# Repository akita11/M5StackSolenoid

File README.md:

# M5StackSolenoid

ソレノイド（[タカハの5Vソレノイド](http://takaha.co.jp/co/product-ss#productWrapSec1)など）を制御するM5Stack用の拡張基板です。
最大4個のソレノイドをON/OFF制御できます。

# 機能

実装するコネクタ・部品によって、以下の2通りの使い方ができます。
- [使い方1] USBコネクタ実装（[タカハの5Vソレノイド](http://takaha.co.jp/co/product-ss#productWrapSec1)用）：以下のようになります

- [使い方2] 2.ネジ端子実装（一般のソレノイド）：以下のようになります

※[スイッチサイエンスで託販売しているもの](https://www.switch-science.com/catalog/6328/)（5Vソレノイド用のショートピン端子が5個付属しています）は、「使い方1」の状態のものです。

# 用意するもの
- M5Stack (Core/Gray等のCore系、またはCore2)
- USB Type-C端子のある電源（ACアダプタ、モバイルバッテリ等。ソレノイド駆動用の電源）
- ソレノイド（用いているnMOS、ダイオードの定格内のものを用いてください）
  - [使い方1] [タカハの5Vソレノイド](http://takaha.co.jp/co/product-ss#productWrapSec1)、microUSBケーブル、[ショートピン端子](http://akizukidenshi.com/catalog/g/gP-03687/)※「タカハの5Vソレノイド」に「ショートピン端子」を差し込んだ状態で使用します
  - [使い方2] ソレノイド、ネジ端子[HT396R-4P](https://ja.aliexpress.com/item/33027266661.html)、IP2721（USB PDで5V以外の電圧をソレノイド駆動に用いる場合：IP2721の使い方の詳細はIP2721のデータシートを参照してください）

# 使い方
1. M5Stackの本体(Core、底板を外した状態)に本ボードを差し込み、USB Type-C端子に電源をつなぎます。
1. M5Stackの以下のGPIOピンに1を与えるとソレノイドがONに、0を与えるとOFFになります。（M5Stackのプログラムは、ArduinoIDE、UI Flow等で開発できます）使用例としてtest.m5f (UI Flowプログラム）を参照してください。
   - Ch.A : GPIO26
   - Ch.B : GPIO12 (Core2ではGPIO27)
   - Ch.C : GPIO13 (Core2ではGPIO19)
   - Ch.D : GPIO5 (Core2ではGPIO33)

※なおソレノイドの番号は、[使い方1]の場合は基板上の[A]-[D]で表示されているUSBコネクタに対応します。[使い方2]の場合は、基板上の"Ch.A"-"Ch.D"の表示に対応し、1つのネジ端子(HT396R)に2個のソレノイドを接続できます。

# Author

Junichi Akita (@akita11, akita@ifdl.jp)

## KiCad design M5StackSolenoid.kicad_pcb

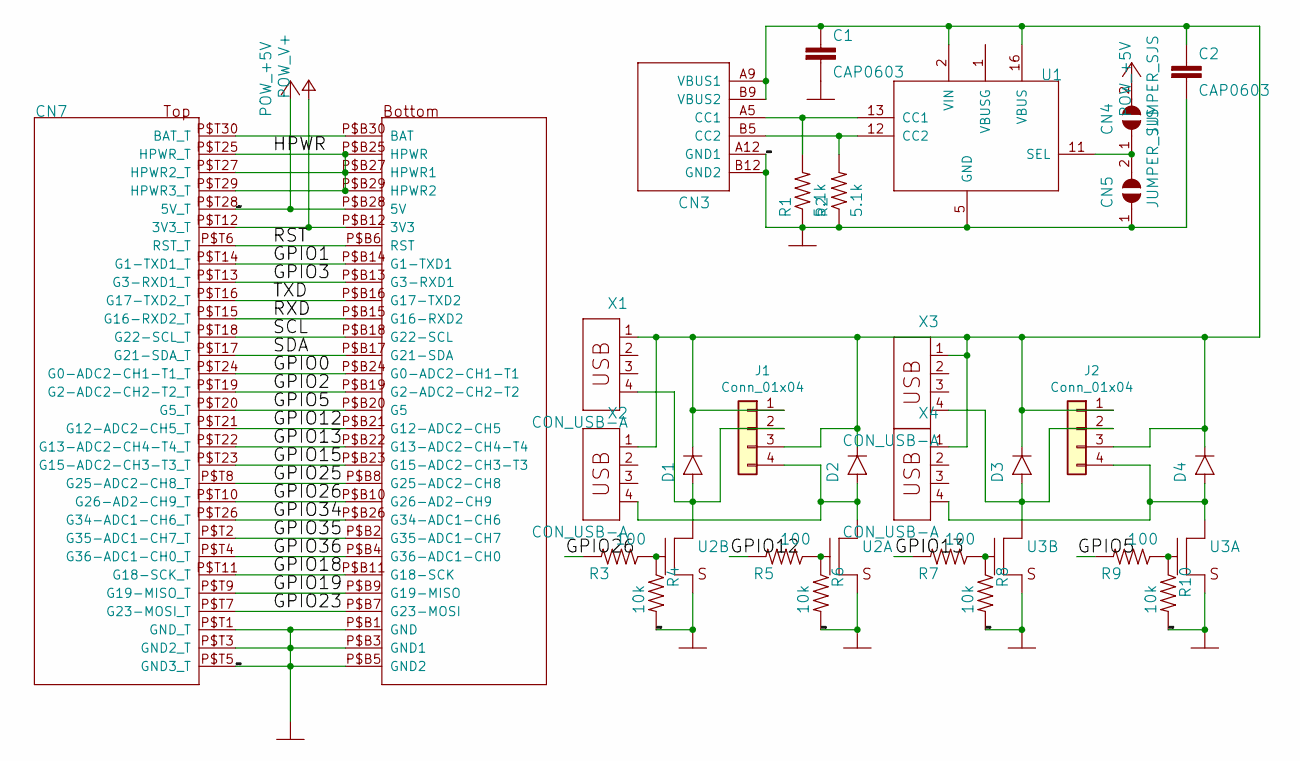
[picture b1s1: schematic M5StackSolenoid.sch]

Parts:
C1, C2: CAP0603; 0603
CN3: CON_USB-C-6; USB-C_6P
CN4, CN5: JUMPER_SJS
CN7: MBUS_SEPNOHOLE; MBUS_SEP_NOHOLENOTCH
D1, D2, D3, D4: DIODESOD123FL; SOD123FL
J1, J2: Conn_01x04; CON_HT396R_4P
R1, R2: 5.1k; 0603
R3, R5, R7, R9: 100; 0603
R4, R6, R8, R10: 10k; 0603
U1: PMC_IP2721; TSSOP16
U2, U3: TR_NMOS_IRF7103; SO08
X1, X2, X3, X4: CON_USB-A; USB-A

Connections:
+5V: CN4.2, CN7.P$B28 (5V), CN7.P$T28 (5V_T)
/GPIO0: CN7.P$B24 (G0-ADC2-CH1-T1), CN7.P$T24 (G0-ADC2-CH1-T1_T)
/GPIO1: CN7.P$B14 (G1-TXD1), CN7.P$T14 (G1-TXD1_T)
/GPIO2: CN7.P$B19 (G2-ADC2-CH2-T2), CN7.P$T19 (G2-ADC2-CH2-T2_T)
/GPIO3: CN7.P$B13 (G3-RXD1), CN7.P$T13 (G3-RXD1_T)
/GPIO5: CN7.P$B20 (G5), CN7.P$T20 (G5_T), R9.2
/GPIO12: CN7.P$B21 (G12-ADC2-CH5), CN7.P$T21 (G12-ADC2-CH5_T), R5.2
/GPIO13: CN7.P$B22 (G13-ADC2-CH4-T4), CN7.P$T22 (G13-ADC2-CH4-T4_T), R7.2
/GPIO15: CN7.P$B23 (G15-ADC2-CH3-T3), CN7.P$T23 (G15-ADC2-CH3-T3_T)
/GPIO18: CN7.P$B11 (G18-SCK), CN7.P$T11 (G18-SCK_T)
/GPIO19: CN7.P$B9 (G19-MISO), CN7.P$T9 (G19-MISO_T)
/GPIO23: CN7.P$B7 (G23-MOSI), CN7.P$T7 (G23-MOSI_T)
/GPIO25: CN7.P$B8 (G25-ADC2-CH8), CN7.P$T8 (G25-ADC2-CH8_T)
/GPIO26: CN7.P$B10 (G26-AD2-CH9), CN7.P$T10 (G26-AD2-CH9_T), R3.2
/GPIO34: CN7.P$B26 (G34-ADC1-CH6), CN7.P$T26 (G34-ADC1-CH6_T)
/GPIO35: CN7.P$B2 (G35-ADC1-CH7), CN7.P$T2 (G35-ADC1-CH7_T)
/GPIO36: CN7.P$B4 (G36-ADC1-CH0), CN7.P$T4 (G36-ADC1-CH0_T)
/HPWR: CN7.P$B25 (HPWR), CN7.P$B27 (HPWR1), CN7.P$B29 (HPWR2), CN7.P$T25 (HPWR_T), CN7.P$T27 (HPWR2_T), CN7.P$T29 (HPWR3_T)
/RST: CN7.P$B6 (RST), CN7.P$T6 (RST_T)
/RXD: CN7.P$B15 (G16-RXD2), CN7.P$T15 (G16-RXD2_T)
/SCL: CN7.P$B18 (G22-SCL), CN7.P$T18 (G22-SCL_T)
/SDA: CN7.P$B17 (G21-SDA), CN7.P$T17 (G21-SDA_T)
/TXD: CN7.P$B16 (G17-TXD2), CN7.P$T16 (G17-TXD2_T)
GND: C1.2, C2.2, CN3.A12 (GND1), CN3.B12 (GND2), CN5.1, CN7.P$B1 (GND), CN7.P$B3 (GND1), CN7.P$B5 (GND2), CN7.P$T1 (GND_T), CN7.P$T3 (GND2_T), CN7.P$T5 (GND3_T), R1.1, R2.1, R4.2, R6.2, R8.2, R10.2, U1.5 (GND), U2.1 (S), U2.3 (S), U3.1 (S), U3.3 (S)
unnamed: C1.1, C2.1, CN3.A9 (VBUS1), CN3.B9 (VBUS2), D1.P$K, D2.P$K, D3.P$K, D4.P$K, J1.1, J1.3, J2.1, J2.3, U1.2 (VIN), U1.16 (VBUS), X1.1, X2.1, X3.1, X4.1
unnamed: CN3.A5 (CC1), R1.2, U1.13 (CC1)
unnamed: CN3.B5 (CC2), R2.2, U1.12 (CC2)
unnamed: CN4.1, CN5.2, U1.11 (SEL)
unnamed: CN7.P$B30 (BAT), CN7.P$T30 (BAT_T)
unnamed: D1.P$A, J1.2, U2.5 (D), X1.4
unnamed: D2.P$A, J1.4, U2.7 (D), X2.4
unnamed: D3.P$A, J2.2, U3.5 (D), X3.4
unnamed: D4.P$A, J2.4, U3.7 (D), X4.4
unnamed: R3.1, R4.1, U2.4 (G)
unnamed: R5.1, R6.1, U2.2 (G)
unnamed: R7.1, R8.1, U3.4 (G)
unnamed: R9.1, R10.1, U3.2 (G)
V+: CN7.P$B12 (3V3), CN7.P$T12 (3V3_T)

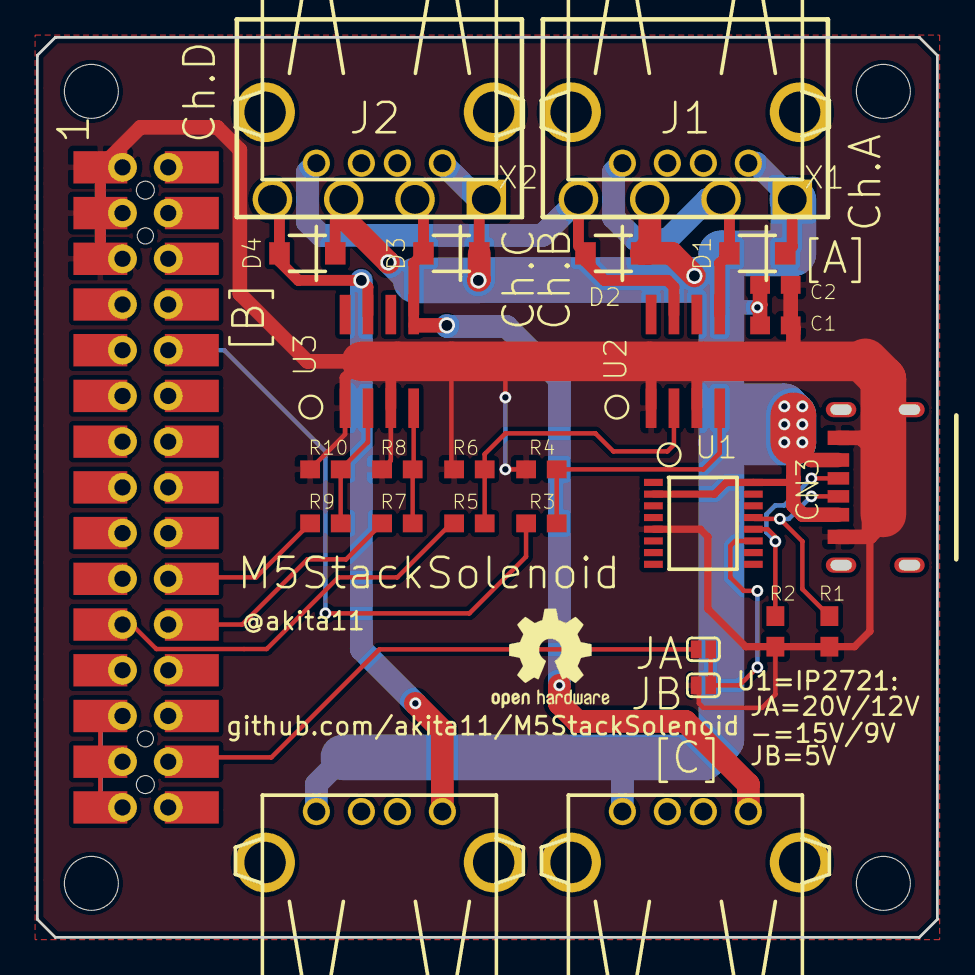
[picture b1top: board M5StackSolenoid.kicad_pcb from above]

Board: 2 copper layers, 50.0 x 50.0 mm, 29 parts (0 on the bottom side), 38 nets.

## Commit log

2020-03-26 ファイル一式とREADMEを追加
2020-04-08 UIFlow用テストプログラムを追加
2020-06-09 readmeに5Vソレノイドのショートピンについて追記
2020-06-09 readmeに追記
2020-09-04 Core2の情報を記載
